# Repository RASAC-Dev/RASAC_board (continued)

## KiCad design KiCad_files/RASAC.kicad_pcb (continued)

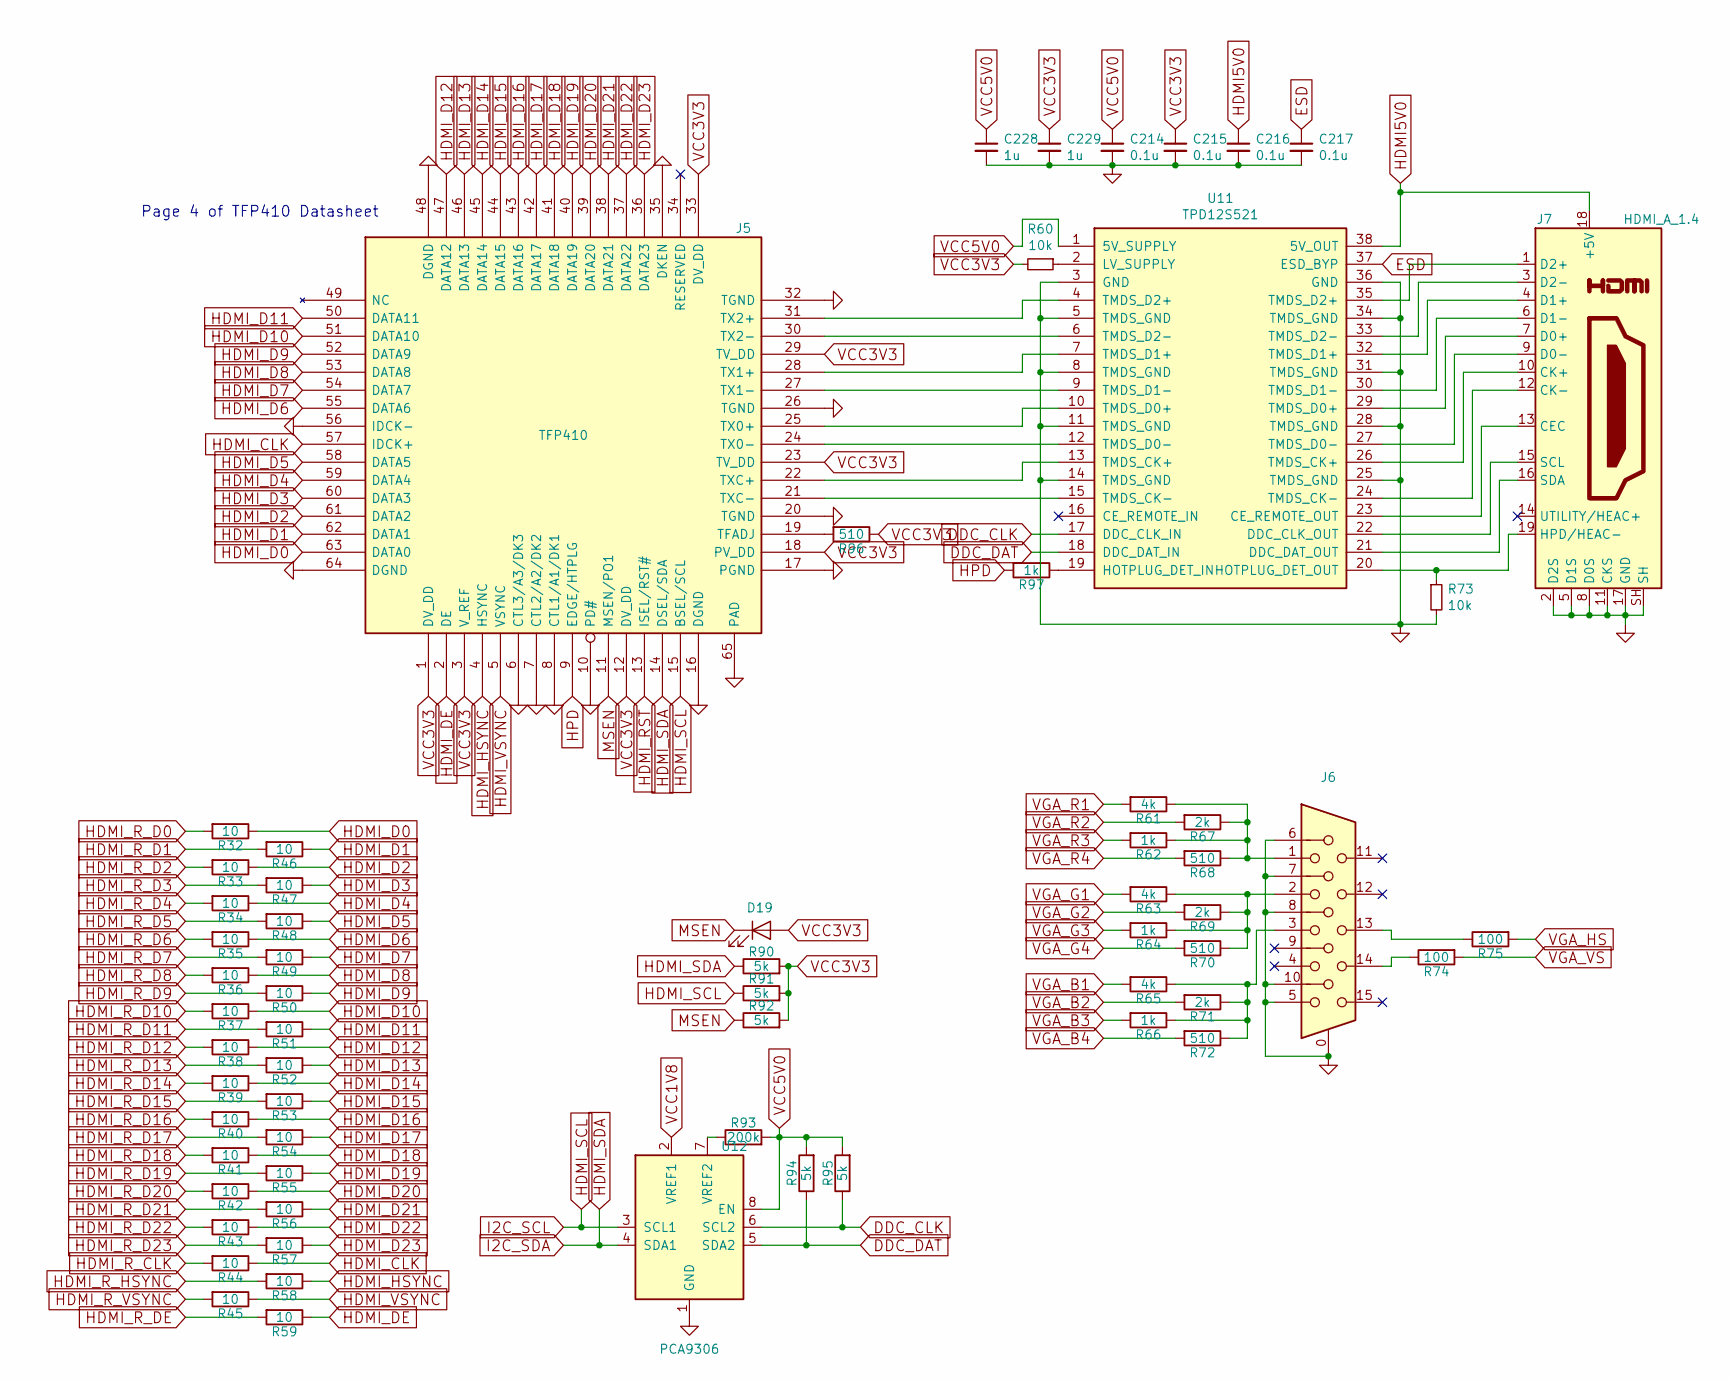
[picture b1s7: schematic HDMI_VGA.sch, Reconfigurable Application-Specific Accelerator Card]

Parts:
C214, C215, C216, C217: 0.1u; C_0805
C228, C229: 1u; C_0805
D19: LED; LED_0603
J5: TFP410; HTQFP-64-1EP_10x10mm_Pitch0.5mm_ThermalPad
J6: DB15_Female_HighDensity_MountingHoles; DSUB-15-HD_Female_Horizontal_Pitch2.29x1.98mm_EdgePinOffset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
J7: HDMI_A_1.4; HDMI_A
R32, R33, R34, R35, R36, R37, R38, R39, R40, R41, R42, R43, R44, R45, R46, R47, R48, R49, R50, R51, R52, R53, R54, R55, R56, R57, R58, R59: 10; R_0603
R60, R73: 10k; R_0805
R61, R63, R65: 4k; R_0805
R62, R64, R66, R97: 1k; R_0805
R67, R69, R71: 2k; R_0805
R68, R70, R72, R96: 510; R_0805
R74, R75: 100; R_0603
R90, R91, R92, R94, R95: 5k; R_0805
R93: 200k; R_0805
U11: TPD12S521; TSSOP-38_4.4x9.7mm_Pitch0.5mm
U12: PCA9306; VSSOP-8_2.4x2.1mm_Pitch0.5mm

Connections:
DDC_CLK: R95.1, U11.17 (DDC_CLK_IN), U12.6 (SCL2)
DDC_DAT: R94.1, U11.18 (DDC_DAT_IN), U12.5 (SDA2)
ESD: C217.1, U11.37 (ESD_BYP)
GND: C214.2, C215.2, C216.2, C217.2, C228.2, C229.2, J5.6 (CTL3/A3/DK3), J5.7 (CTL2/A2/DK2), J5.8 (CTL1/A1/DK1), J5.10 (PD#), J5.16 (DGND), J5.17 (PGND), J5.20 (TGND), J5.26 (TGND), J5.32 (TGND), J5.35 (DKEN), J5.48 (DGND), J5.56 (IDCK-), J5.64 (DGND), J5.65 (PAD), J6.0, J6.5, J6.6, J6.7, J6.8, J6.10, J7.2 (D2S), J7.5 (D1S), J7.8 (D0S), J7.11 (CKS), J7.17 (GND), J7.SH, R73.2, U11.3 (GND), U11.5 (TMDS_GND), U11.8 (TMDS_GND), U11.11 (TMDS_GND), U11.14 (TMDS_GND), U11.25 (TMDS_GND), U11.28 (TMDS_GND), U11.31 (TMDS_GND), U11.34 (TMDS_GND), U11.36 (GND), U12.1 (GND); also elsewhere on the board
HDMI5V0: C216.1, J7.18 (+5V), U11.38 (5V_OUT)
HDMI_CLK: J5.57 (IDCK+), R44.1
HDMI_D0: J5.63 (DATA0), R32.1
HDMI_D1: J5.62 (DATA1), R46.1
HDMI_D2: J5.61 (DATA2), R33.1
HDMI_D3: J5.60 (DATA3), R47.1
HDMI_D4: J5.59 (DATA4), R34.1
HDMI_D5: J5.58 (DATA5), R48.1
HDMI_D6: J5.55 (DATA6), R35.1
HDMI_D7: J5.54 (DATA7), R49.1
HDMI_D8: J5.53 (DATA8), R36.1
HDMI_D9: J5.52 (DATA9), R50.1
HDMI_D10: J5.51 (DATA10), R37.1
HDMI_D11: J5.50 (DATA11), R51.1
HDMI_D12: J5.47 (DATA12), R38.1
HDMI_D13: J5.46 (DATA13), R52.1
HDMI_D14: J5.45 (DATA14), R39.1
HDMI_D15: J5.44 (DATA15), R53.1
HDMI_D16: J5.43 (DATA16), R40.1
HDMI_D17: J5.42 (DATA17), R54.1
HDMI_D18: J5.41 (DATA18), R41.1
HDMI_D19: J5.40 (DATA19), R55.1
HDMI_D20: J5.39 (DATA20), R42.1
HDMI_D21: J5.38 (DATA21), R56.1
HDMI_D22: J5.37 (DATA22), R43.1
HDMI_D23: J5.36 (DATA23), R57.1
HDMI_DE: J5.2 (DE), R59.1
HDMI_HSYNC: J5.4 (HSYNC), R58.1
HDMI_RST: J5.13 (ISEL/RST#); also elsewhere on the board
HDMI_R_CLK: R44.2; also elsewhere on the board
HDMI_R_D0: R32.2; also elsewhere on the board
HDMI_R_D1: R46.2; also elsewhere on the board
HDMI_R_D2: R33.2; also elsewhere on the board
HDMI_R_D3: R47.2; also elsewhere on the board
HDMI_R_D4: R34.2; also elsewhere on the board
HDMI_R_D5: R48.2; also elsewhere on the board
HDMI_R_D6: R35.2; also elsewhere on the board
HDMI_R_D7: R49.2; also elsewhere on the board
HDMI_R_D8: R36.2; also elsewhere on the board
HDMI_R_D9: R50.2; also elsewhere on the board
HDMI_R_D10: R37.2; also elsewhere on the board
HDMI_R_D11: R51.2; also elsewhere on the board
HDMI_R_D12: R38.2; also elsewhere on the board
HDMI_R_D13: R52.2; also elsewhere on the board
HDMI_R_D14: R39.2; also elsewhere on the board
HDMI_R_D15: R53.2; also elsewhere on the board
HDMI_R_D16: R40.2; also elsewhere on the board
HDMI_R_D17: R54.2; also elsewhere on the board
HDMI_R_D18: R41.2; also elsewhere on the board
HDMI_R_D19: R55.2; also elsewhere on the board
HDMI_R_D20: R42.2; also elsewhere on the board
HDMI_R_D21: R56.2; also elsewhere on the board
HDMI_R_D22: R43.2; also elsewhere on the board
HDMI_R_D23: R57.2; also elsewhere on the board
HDMI_R_DE: R59.2; also elsewhere on the board
HDMI_R_HSYNC: R58.2; also elsewhere on the board
HDMI_R_VSYNC: R45.2; also elsewhere on the board
HDMI_SCL: J5.15 (BSEL/SCL), R91.1, U12.3 (SCL1); also elsewhere on the board
HDMI_SDA: J5.14 (DSEL/SDA), R90.1, U12.4 (SDA1); also elsewhere on the board
HDMI_VSYNC: J5.5 (VSYNC), R45.1
HPD: J5.9 (EDGE/HTPLG), R97.2
MSEN: D19.1 (K), J5.11 (MSEN/PO1), R92.1
unnamed: J5.19 (TFADJ), R96.2
unnamed: J5.21 (TXC-), U11.15 (TMDS_CK-)
unnamed: J5.22 (TXC+), U11.13 (TMDS_CK+)
unnamed: J5.24 (TX0-), U11.12 (TMDS_D0-)
unnamed: J5.25 (TX0+), U11.10 (TMDS_D0+)
unnamed: J5.27 (TX1-), U11.9 (TMDS_D1-)
unnamed: J5.28 (TX1+), U11.7 (TMDS_D1+)
unnamed: J5.30 (TX2-), U11.6 (TMDS_D2-)
unnamed: J5.31 (TX2+), U11.4 (TMDS_D2+)
unnamed: J6.1, R61.1, R62.1, R67.1, R68.1
unnamed: J6.2, R63.1, R64.1, R69.1, R70.1
unnamed: J6.3, R65.1, R66.1, R71.1, R72.1
unnamed: J6.13, R75.1
unnamed: J6.14, R74.1
unnamed: J7.1 (D2+), U11.35 (TMDS_D2+)
unnamed: J7.3 (D2-), U11.33 (TMDS_D2-)
unnamed: J7.4 (D1+), U11.32 (TMDS_D1+)
unnamed: J7.6 (D1-), U11.30 (TMDS_D1-)
unnamed: J7.7 (D0+), U11.29 (TMDS_D0+)
unnamed: J7.9 (D0-), U11.27 (TMDS_D0-)
unnamed: J7.10 (CK+), U11.26 (TMDS_CK+)
unnamed: J7.12 (CK-), U11.24 (TMDS_CK-)
unnamed: J7.13 (CEC), U11.23 (CE_REMOTE_OUT)
unnamed: J7.15 (SCL), U11.22 (DDC_CLK_OUT)
unnamed: J7.16 (SDA), U11.21 (DDC_DAT_OUT)
unnamed: J7.19 (HPD/HEAC-), R73.1, U11.20 (HOTPLUG_DET_OUT)
unnamed: R60.1, U11.2 (LV_SUPPLY)
unnamed: R93.1, U12.7 (VREF2)
unnamed: R97.1, U11.19 (HOTPLUG_DET_IN)
VCC1V8: U12.2 (VREF1); also elsewhere on the board
VCC3V3: C215.1, C229.1, D19.2 (A), J5.1 (DV_DD), J5.3 (V_REF), J5.12 (DV_DD), J5.18 (PV_DD), J5.23 (TV_DD), J5.29 (TV_DD), J5.33 (DV_DD), R60.2, R90.2, R91.2, R92.2, R96.1; also elsewhere on the board
VCC5V0: C214.1, C228.1, R93.2, R94.2, R95.2, U11.1 (5V_SUPPLY), U12.8 (EN); also elsewhere on the board
VGA_B1: R65.2; also elsewhere on the board
VGA_B2: R71.2; also elsewhere on the board
VGA_B3: R66.2; also elsewhere on the board
VGA_B4: R72.2; also elsewhere on the board
VGA_G1: R63.2; also elsewhere on the board
VGA_G2: R69.2; also elsewhere on the board
VGA_G3: R64.2; also elsewhere on the board
VGA_G4: R70.2; also elsewhere on the board
VGA_HS: R75.2; also elsewhere on the board
VGA_R1: R61.2; also elsewhere on the board
VGA_R2: R67.2; also elsewhere on the board
VGA_R3: R62.2; also elsewhere on the board
VGA_R4: R68.2; also elsewhere on the board
VGA_VS: R74.2; also elsewhere on the board

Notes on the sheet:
Page 4 of TFP410 Datasheet

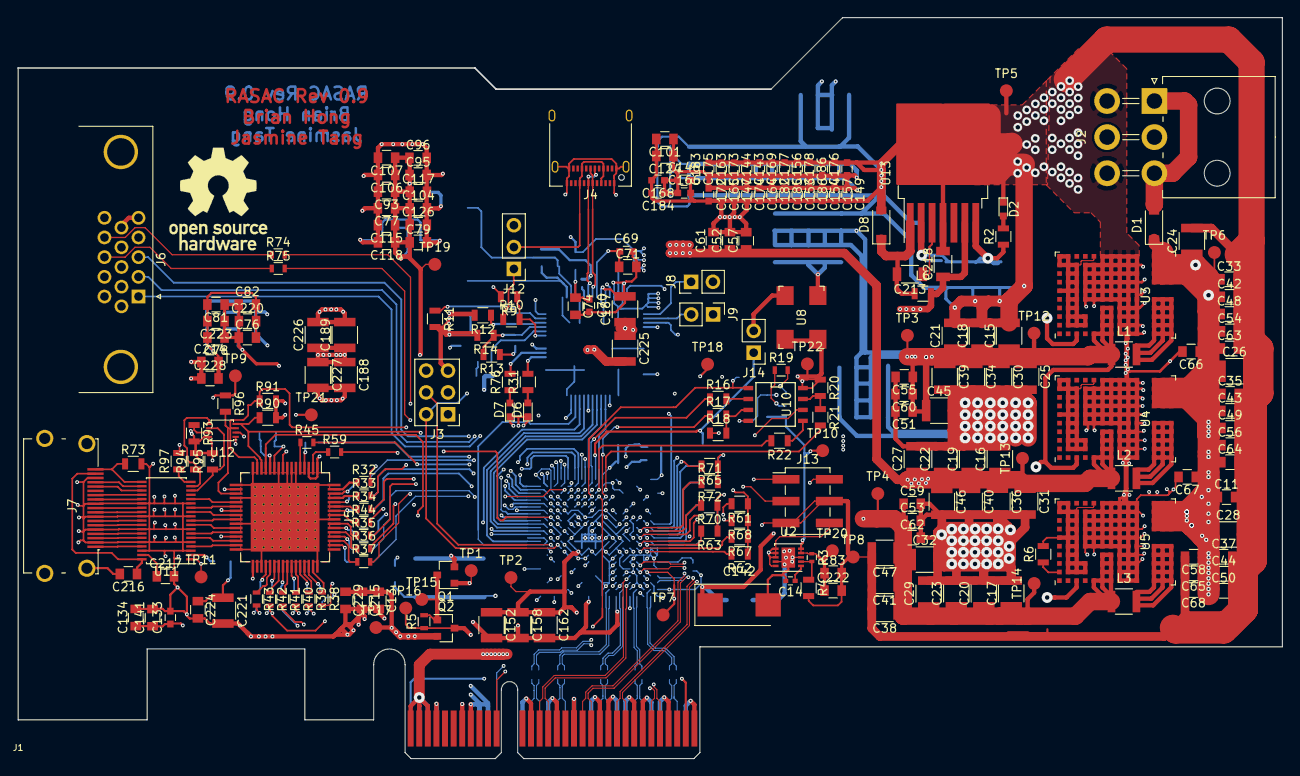
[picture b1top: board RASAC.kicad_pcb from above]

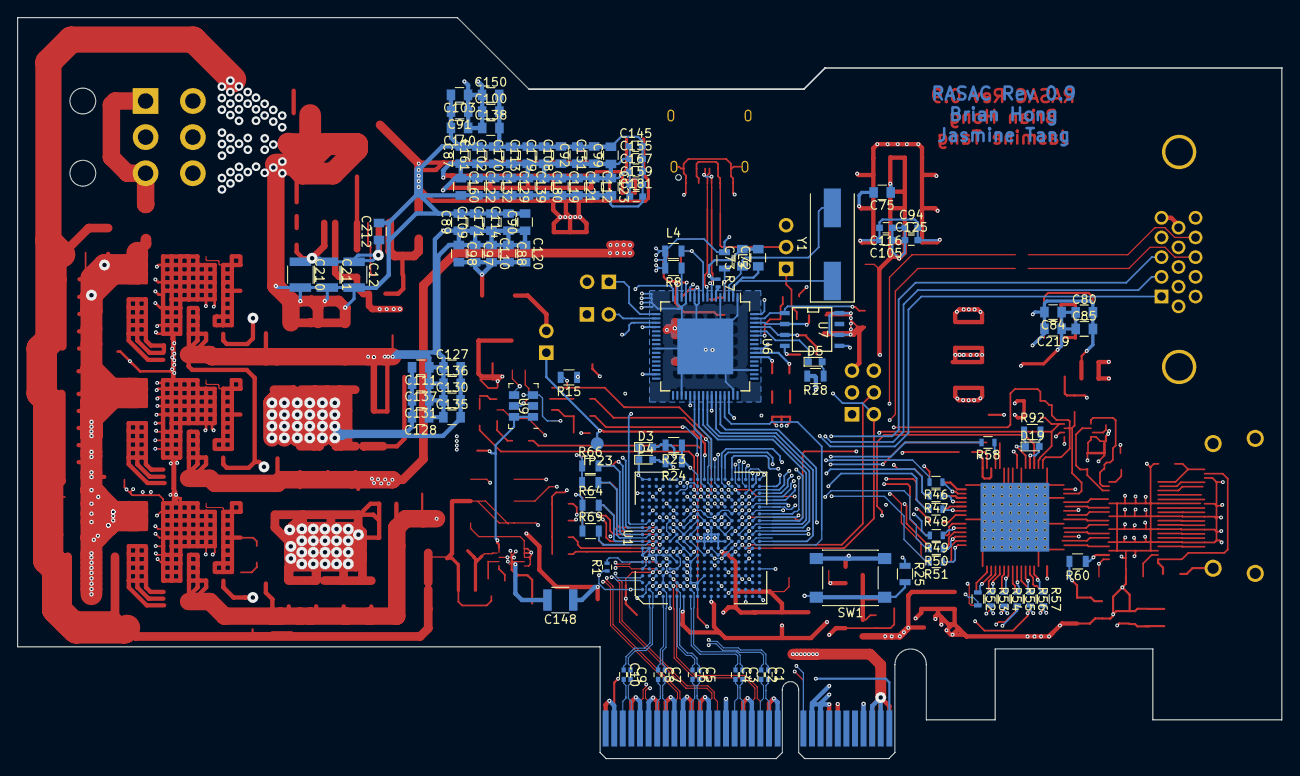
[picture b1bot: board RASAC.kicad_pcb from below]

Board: 6 copper layers, 147.0 x 86.2 mm, 356 parts (115 on the bottom side), 218 nets.

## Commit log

2018-12-17 Added KiCad files
    Schematics done:
    FPGA
    Voltage Regulators
    Configuration
    Debug (JTAG + UART)
    PCIe Interface
2018-12-17 Cleanup
    Removed old schematic files
2018-12-17 Directory Structure
2018-12-17 Upgraded FPGA
    Changed FPGA part from XC7A25T to XC7A35T
2018-12-17 Added some artwork for poster
2018-12-17 Added SYSCLK
    Changed EMCCLK from SiT8103 to SiT8209 because Digikey didn't have.
    Added SiT9102 200MHz for SYSCLK
2018-12-18 Added HDMI transmitter chip
    Also added resistors and moved HDMI data pins around on FPGA side
2018-12-18 New FPGA_modules branch
2018-12-18 Separated out Docs and FPGA_modules
2018-12-18 Added VGA
2018-12-18 DDR RAM 32 bits instead of 64bits
    Don't have enough pins :(
2018-12-18 Cleanup for demo/presentation
    Merged Config and Debug sheets.
    Added GPIO for remaining pins.
    Annotations.
2019-01-29 Added Decoupling Caps?
2019-01-30 Cleanup + Update to KiCad 5.0 + DDR2
    Updated to KiCad 5, which re-organized libraries, so corrected them to not need RASAC-rescue.lib.
    Also cleaned up some stuff.
    DDR4 has been removed and in place will be DDR2.
2019-01-30 Minor fixes
    Still fixing from KiCad update
2019-02-02 More fixes
2019-02-02 Added TPD12S521 Port Protection for HDMI
2019-02-03 Finished HDMI. Added I2C
2019-02-24 Config_Debug and PCIe sheets look done
    Added jumpers to JTAG chain.
    Placed NCs on not used pins.
    PCIe_PRSNT_B should be connected to the furthest PCIe_PRSNT_#.
2019-02-24 HDMI_VGA is good. Need 5V for HDMI
    TODO: DDR2, connections, power
2019-02-26 Cleanup for DRC and HDMI. HDMI and DDR2 looks good
    DRC returns 5 errors with POWEROUTPUT-POWEROUTPUT set as good.
    3 of them come from 3V3 since it's being driven from a MOSFET.
    1 of them from VCC5V0 not yet supplied.
    1 of them from USB_VBUS not set as output.
    TODO:
    5V supply for HDMI
2019-02-26 Added 5V supply for HDMI.
    Added jumper for USB-C power
    TODO:
    Add more jumpers (EMCCLK and Config)
    Add lots of test points
2019-02-27 Added more caps and jumpers for EMCCLK & Config
2019-02-27 More caps and added lots of test points
2019-02-27 Annotations and proper connections
2019-02-27 Attempted to add USB-C and then reverted
    File still saved locally
2019-02-27 Started mapping footprints
2019-02-27 Finished capacitor footprints
    Total cost: ~$55
2019-02-27 Almost done with footprints. See issues below
    Inductors left to do.
    Others without footprints need custom.
    PI3420 is out of stock...
    LM2676 symbol should be re-drawn for TO-263-7
    Total cost: ~$214
2019-02-27 Replaced PCIe x4 footprint
    Footprint generated with https://github.com/dlharmon/footgen
2019-02-27 Fixed LM2676
2019-02-27 Should've been part of previous commit
2019-02-27 LGA-123 Drawn and added
    PI3420 will come from Mouser...
2019-02-28 Drew some more footprints
    BTW another DRC error popped up since I2C level shifter now uses VCC5V0
    TODO:
    FPGA footprint + Inductors and FETs
2019-02-28 Inductors and FETs footprints
    TODO:
    FPGA and HDMI foorprints
    Layout
2019-02-28 Drew FPGA and HDMI footprints
    Ready for layout...?
2019-02-28 Schematics reformatted for A size
    I think rev 1.0 is ready
2019-03-06 Fixes during layout
    Changed FT2232HL footprint to one with external pad
    Made LGA123 (PI34XX) pins into blocks
    Added labels for PCIe to let KiCad do differential pair routing
    Removed some ground connections in SGND in PI34XX
2019-03-06 Initial layout (in progress)
    Power input finished (?)
    First attempt at PCIe connections; will probably have to re-do
    Started on RAM
2019-03-19 PCB Layout
    Don't remember what changed, but gonna push before my computer dies again
2019-03-19 Initial FPGA routing + 3D RAM
    Slowly losing insanity while listening to WII music for hours
2019-03-20 PCIe + RAM Layout?
    Is this PCIe even going to work...?
2019-03-24 RAM+FPGA Attempt #1
    Oh geez
2019-03-26 RAM+FPGA Attempt #2
    Plus some power connections
2019-03-26 OH MY GOD
2019-03-31 More RAM routing
2019-04-01 Purged RAM (SCH)
    Was taking way too lon of a time which I didn't have
    Also using larger resistors and capacitors than 0402 and 0201 (expect a very few)
2019-04-01 Minor wiring fix
2019-04-01 Purged RAM (PCB) and updated RC footprints
2019-04-01 UART + JTAG + half of HDMI
    Also resized HDMI resistors from 1206 to 0603
2019-04-02 More HDMI
2019-04-02 Some more HDMI + power
2019-04-02 HDMI Done?
2019-04-02 Almost done
    Just gotta do capacitors, I think
2019-04-03 Am... Am I done...?
2019-04-03 Added text + logo + output files
